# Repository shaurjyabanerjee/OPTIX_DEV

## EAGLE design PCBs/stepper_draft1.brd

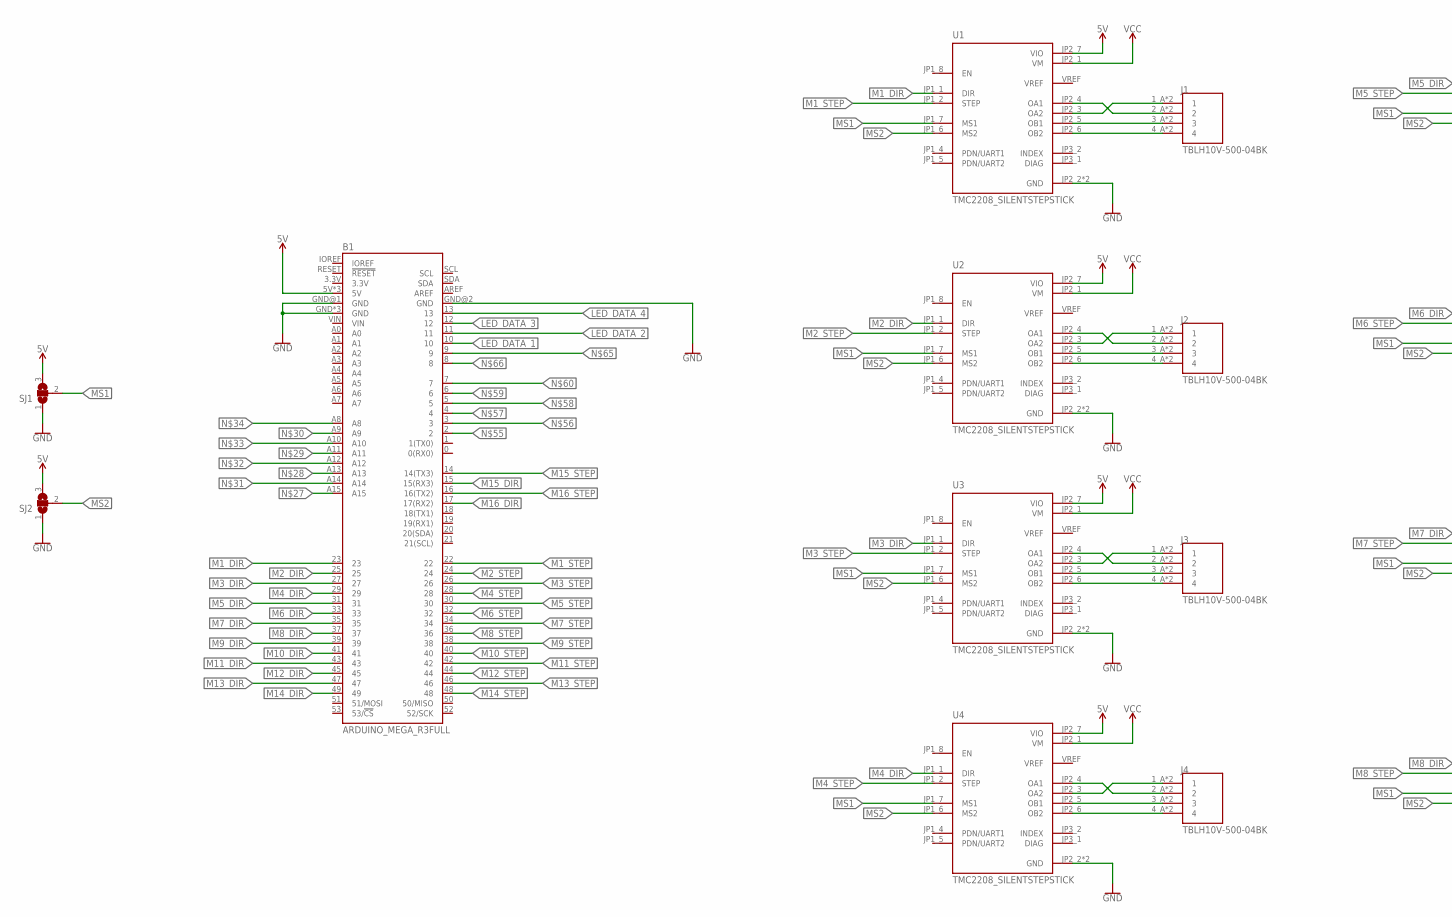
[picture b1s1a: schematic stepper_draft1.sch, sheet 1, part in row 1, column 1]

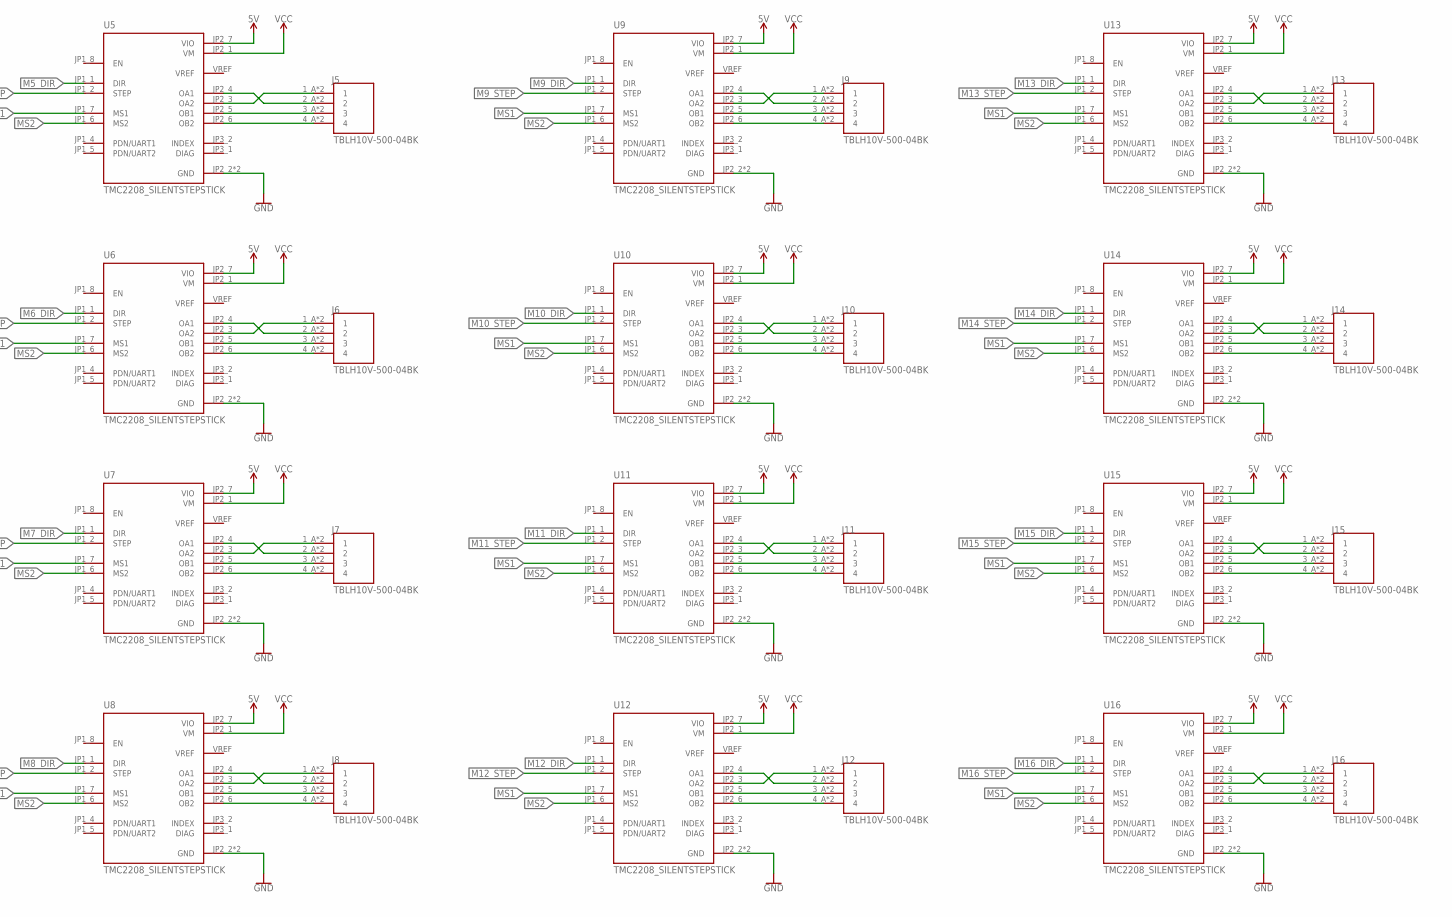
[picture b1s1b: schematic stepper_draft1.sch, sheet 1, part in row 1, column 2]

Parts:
B1: ARDUINO_MEGA_R3FULL; ARDUINO_MEGA_NO_SILK
J1, J2, J3, J4, J5, J6, J7, J8, J9, J10, J11, J12, J13, J14, J15, J16: TBLH10V-500-04BK; CUI_TBLH10V-500-04BK
SJ1, SJ2: SJ2W; SJ_2
U1, U2, U3, U4, U5, U6, U7, U8, U9, U10, U11, U12, U13, U14, U15, U16: TMC2208_SILENTSTEPSTICK; MODULE_TMC2208_SILENTSTEPSTICK

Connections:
5V: B1.5V, B1.5V@1 (5V), B1.5V@2 (5V), SJ1.3, SJ2.3, U1.JP2_7 (VIO), U2.JP2_7 (VIO), U3.JP2_7 (VIO), U4.JP2_7 (VIO), U5.JP2_7 (VIO), U6.JP2_7 (VIO), U7.JP2_7 (VIO), U8.JP2_7 (VIO), U9.JP2_7 (VIO), U10.JP2_7 (VIO), U11.JP2_7 (VIO), U12.JP2_7 (VIO), U13.JP2_7 (VIO), U14.JP2_7 (VIO), U15.JP2_7 (VIO), U16.JP2_7 (VIO)
GND: B1.GND, B1.GND@1 (GND), B1.GND@2 (GND), B1.GND@3 (GND), B1.GND@4 (GND), SJ1.1, SJ2.1, U1.JP2_2 (GND), U1.JP2_8 (GND), U2.JP2_2 (GND), U2.JP2_8 (GND), U3.JP2_2 (GND), U3.JP2_8 (GND), U4.JP2_2 (GND), U4.JP2_8 (GND), U5.JP2_2 (GND), U5.JP2_8 (GND), U6.JP2_2 (GND), U6.JP2_8 (GND), U7.JP2_2 (GND), U7.JP2_8 (GND), U8.JP2_2 (GND), U8.JP2_8 (GND), U9.JP2_2 (GND), U9.JP2_8 (GND), U10.JP2_2 (GND), U10.JP2_8 (GND), U11.JP2_2 (GND), U11.JP2_8 (GND), U12.JP2_2 (GND), U12.JP2_8 (GND), U13.JP2_2 (GND), U13.JP2_8 (GND), U14.JP2_2 (GND), U14.JP2_8 (GND), U15.JP2_2 (GND), U15.JP2_8 (GND), U16.JP2_2 (GND), U16.JP2_8 (GND); also elsewhere on the board
LED_DATA_1: B1.10; also elsewhere on the board
LED_DATA_2: B1.11; also elsewhere on the board
LED_DATA_3: B1.12; also elsewhere on the board
LED_DATA_4: B1.13; also elsewhere on the board
M1_DIR: B1.23, U1.JP1_1 (DIR)
M1_STEP: B1.22, U1.JP1_2 (STEP)
M2_DIR: B1.25, U2.JP1_1 (DIR)
M2_STEP: B1.24, U2.JP1_2 (STEP)
M3_DIR: B1.27, U3.JP1_1 (DIR)
M3_STEP: B1.26, U3.JP1_2 (STEP)
M4_DIR: B1.29, U4.JP1_1 (DIR)
M4_STEP: B1.28, U4.JP1_2 (STEP)
M5_DIR: B1.31, U5.JP1_1 (DIR)
M5_STEP: B1.30, U5.JP1_2 (STEP)
M6_DIR: B1.33, U6.JP1_1 (DIR)
M6_STEP: B1.32, U6.JP1_2 (STEP)
M7_DIR: B1.35, U7.JP1_1 (DIR)
M7_STEP: B1.34, U7.JP1_2 (STEP)
M8_DIR: B1.37, U8.JP1_1 (DIR)
M8_STEP: B1.36, U8.JP1_2 (STEP)
M9_DIR: B1.39, U9.JP1_1 (DIR)
M9_STEP: B1.38, U9.JP1_2 (STEP)
M10_DIR: B1.41, U10.JP1_1 (DIR)
M10_STEP: B1.40, U10.JP1_2 (STEP)
M11_DIR: B1.43, U11.JP1_1 (DIR)
M11_STEP: B1.42, U11.JP1_2 (STEP)
M12_DIR: B1.45, U12.JP1_1 (DIR)
M12_STEP: B1.44, U12.JP1_2 (STEP)
M13_DIR: B1.47, U13.JP1_1 (DIR)
M13_STEP: B1.46, U13.JP1_2 (STEP)
M14_DIR: B1.49, U14.JP1_1 (DIR)
M14_STEP: B1.48, U14.JP1_2 (STEP)
M15_DIR: B1.15 (15(RX3)), U15.JP1_1 (DIR)
M15_STEP: B1.14 (14(TX3)), U15.JP1_2 (STEP)
M16_DIR: B1.17 (17(RX2)), U16.JP1_1 (DIR)
M16_STEP: B1.16 (16(TX2)), U16.JP1_2 (STEP)
MS1: SJ1.2, U1.JP1_7 (MS1), U2.JP1_7 (MS1), U3.JP1_7 (MS1), U4.JP1_7 (MS1), U5.JP1_7 (MS1), U6.JP1_7 (MS1), U7.JP1_7 (MS1), U8.JP1_7 (MS1), U9.JP1_7 (MS1), U10.JP1_7 (MS1), U11.JP1_7 (MS1), U12.JP1_7 (MS1), U13.JP1_7 (MS1), U14.JP1_7 (MS1), U15.JP1_7 (MS1), U16.JP1_7 (MS1)
MS2: SJ2.2, U1.JP1_6 (MS2), U2.JP1_6 (MS2), U3.JP1_6 (MS2), U4.JP1_6 (MS2), U5.JP1_6 (MS2), U6.JP1_6 (MS2), U7.JP1_6 (MS2), U8.JP1_6 (MS2), U9.JP1_6 (MS2), U10.JP1_6 (MS2), U11.JP1_6 (MS2), U12.JP1_6 (MS2), U13.JP1_6 (MS2), U14.JP1_6 (MS2), U15.JP1_6 (MS2), U16.JP1_6 (MS2)
unnamed: J1.4_A (4), J1.4_B (4), U1.JP2_6 (OB2)
unnamed: J1.3_A (3), J1.3_B (3), U1.JP2_5 (OB1)
unnamed: J1.2_A (2), J1.2_B (2), U1.JP2_4 (OA1)
unnamed: J1.1_A (1), J1.1_B (1), U1.JP2_3 (OA2)
unnamed: J2.4_A (4), J2.4_B (4), U2.JP2_6 (OB2)
unnamed: J2.3_A (3), J2.3_B (3), U2.JP2_5 (OB1)
unnamed: J2.2_A (2), J2.2_B (2), U2.JP2_4 (OA1)
unnamed: J2.1_A (1), J2.1_B (1), U2.JP2_3 (OA2)
unnamed: J3.4_A (4), J3.4_B (4), U3.JP2_6 (OB2)
unnamed: J3.3_A (3), J3.3_B (3), U3.JP2_5 (OB1)
unnamed: J3.2_A (2), J3.2_B (2), U3.JP2_4 (OA1)
unnamed: J3.1_A (1), J3.1_B (1), U3.JP2_3 (OA2)
unnamed: J4.4_A (4), J4.4_B (4), U4.JP2_6 (OB2)
unnamed: J4.3_A (3), J4.3_B (3), U4.JP2_5 (OB1)
unnamed: J4.2_A (2), J4.2_B (2), U4.JP2_4 (OA1)
unnamed: J4.1_A (1), J4.1_B (1), U4.JP2_3 (OA2)
unnamed: J5.4_A (4), J5.4_B (4), U5.JP2_6 (OB2)
unnamed: J5.3_A (3), J5.3_B (3), U5.JP2_5 (OB1)
unnamed: J5.2_A (2), J5.2_B (2), U5.JP2_4 (OA1)
unnamed: J5.1_A (1), J5.1_B (1), U5.JP2_3 (OA2)
unnamed: J6.4_A (4), J6.4_B (4), U6.JP2_6 (OB2)
unnamed: J6.3_A (3), J6.3_B (3), U6.JP2_5 (OB1)
unnamed: J6.2_A (2), J6.2_B (2), U6.JP2_4 (OA1)
unnamed: J6.1_A (1), J6.1_B (1), U6.JP2_3 (OA2)
unnamed: J7.4_A (4), J7.4_B (4), U7.JP2_6 (OB2)
unnamed: J7.3_A (3), J7.3_B (3), U7.JP2_5 (OB1)
unnamed: J7.2_A (2), J7.2_B (2), U7.JP2_4 (OA1)
unnamed: J7.1_A (1), J7.1_B (1), U7.JP2_3 (OA2)
unnamed: J8.4_A (4), J8.4_B (4), U8.JP2_6 (OB2)
unnamed: J8.3_A (3), J8.3_B (3), U8.JP2_5 (OB1)
unnamed: J8.2_A (2), J8.2_B (2), U8.JP2_4 (OA1)
unnamed: J8.1_A (1), J8.1_B (1), U8.JP2_3 (OA2)
unnamed: J13.4_A (4), J13.4_B (4), U13.JP2_6 (OB2)
unnamed: J13.3_A (3), J13.3_B (3), U13.JP2_5 (OB1)
unnamed: J13.2_A (2), J13.2_B (2), U13.JP2_4 (OA1)
unnamed: J13.1_A (1), J13.1_B (1), U13.JP2_3 (OA2)
unnamed: J14.4_A (4), J14.4_B (4), U14.JP2_6 (OB2)
unnamed: J14.3_A (3), J14.3_B (3), U14.JP2_5 (OB1)
unnamed: J14.2_A (2), J14.2_B (2), U14.JP2_4 (OA1)
unnamed: J14.1_A (1), J14.1_B (1), U14.JP2_3 (OA2)
unnamed: J9.4_A (4), J9.4_B (4), U9.JP2_6 (OB2)
unnamed: J9.3_A (3), J9.3_B (3), U9.JP2_5 (OB1)
unnamed: J9.2_A (2), J9.2_B (2), U9.JP2_4 (OA1)
unnamed: J9.1_A (1), J9.1_B (1), U9.JP2_3 (OA2)
unnamed: J10.4_A (4), J10.4_B (4), U10.JP2_6 (OB2)
unnamed: J10.3_A (3), J10.3_B (3), U10.JP2_5 (OB1)
unnamed: J10.2_A (2), J10.2_B (2), U10.JP2_4 (OA1)
unnamed: J10.1_A (1), J10.1_B (1), U10.JP2_3 (OA2)
unnamed: J11.4_A (4), J11.4_B (4), U11.JP2_6 (OB2)
unnamed: J11.3_A (3), J11.3_B (3), U11.JP2_5 (OB1)
unnamed: J11.2_A (2), J11.2_B (2), U11.JP2_4 (OA1)
unnamed: J11.1_A (1), J11.1_B (1), U11.JP2_3 (OA2)
unnamed: J12.4_A (4), J12.4_B (4), U12.JP2_6 (OB2)
unnamed: J12.3_A (3), J12.3_B (3), U12.JP2_5 (OB1)
unnamed: J12.2_A (2), J12.2_B (2), U12.JP2_4 (OA1)
unnamed: J12.1_A (1), J12.1_B (1), U12.JP2_3 (OA2)
unnamed: J15.4_A (4), J15.4_B (4), U15.JP2_6 (OB2)
unnamed: J15.3_A (3), J15.3_B (3), U15.JP2_5 (OB1)
unnamed: J15.2_A (2), J15.2_B (2), U15.JP2_4 (OA1)
unnamed: J15.1_A (1), J15.1_B (1), U15.JP2_3 (OA2)
unnamed: J16.4_A (4), J16.4_B (4), U16.JP2_6 (OB2)
unnamed: J16.3_A (3), J16.3_B (3), U16.JP2_5 (OB1)
unnamed: J16.2_A (2), J16.2_B (2), U16.JP2_4 (OA1)
unnamed: J16.1_A (1), J16.1_B (1), U16.JP2_3 (OA2)
VCC: U1.JP2_1 (VM), U2.JP2_1 (VM), U3.JP2_1 (VM), U4.JP2_1 (VM), U5.JP2_1 (VM), U6.JP2_1 (VM), U7.JP2_1 (VM), U8.JP2_1 (VM), U9.JP2_1 (VM), U10.JP2_1 (VM), U11.JP2_1 (VM), U12.JP2_1 (VM), U13.JP2_1 (VM), U14.JP2_1 (VM), U15.JP2_1 (VM), U16.JP2_1 (VM)

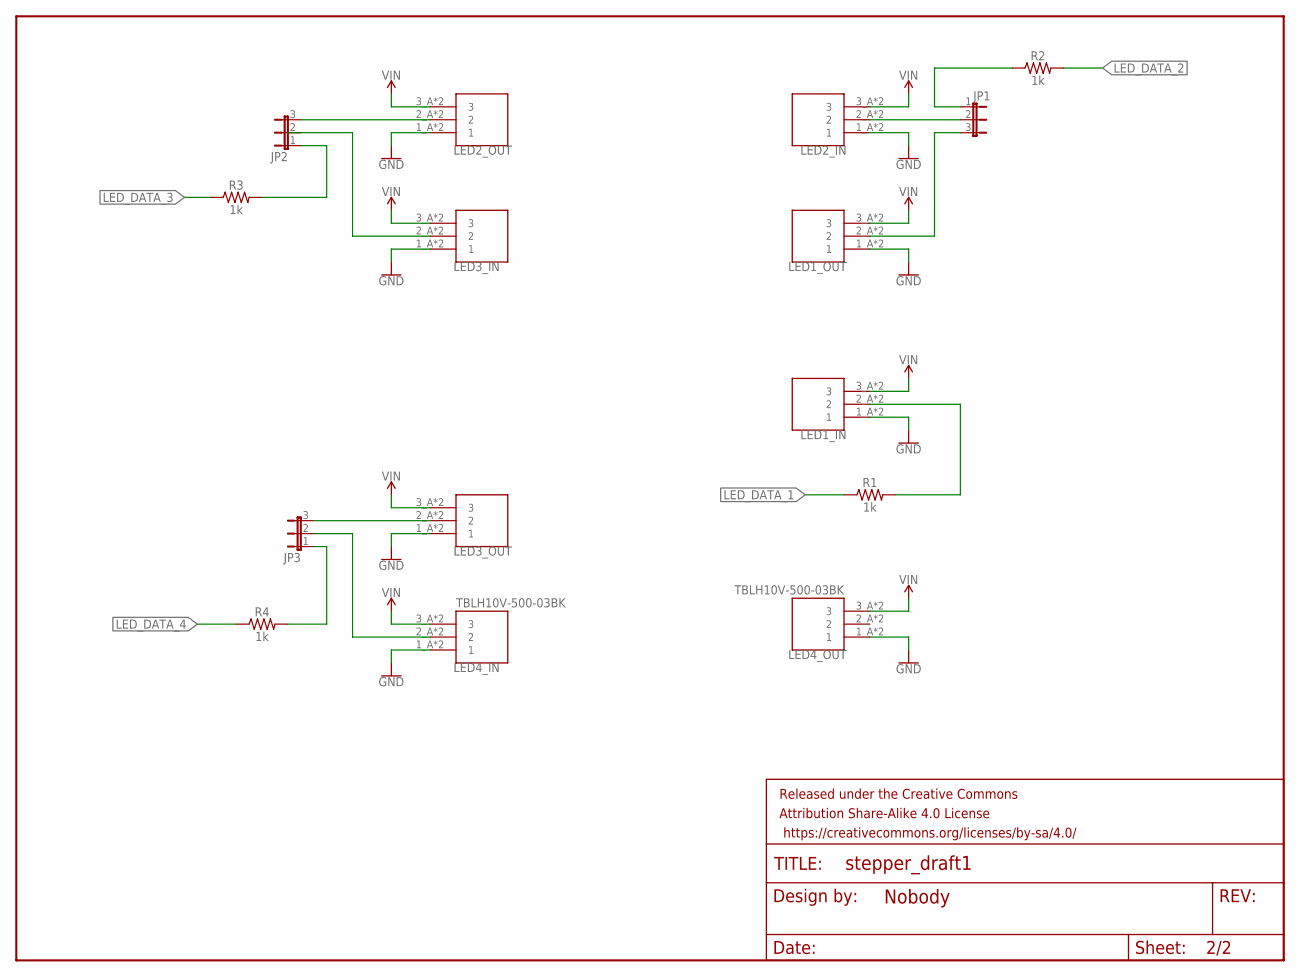
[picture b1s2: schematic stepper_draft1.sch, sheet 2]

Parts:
FRAME1: FRAME-LETTERNO_PACKAGE; DUMMY
JP1, JP2, JP3: JP2E; JP2
LED1_IN, LED1_OUT, LED2_IN, LED2_OUT, LED3_IN, LED3_OUT, LED4_IN, LED4_OUT: TBLH10V-500-03BK; CUI_TBLH10V-500-03BK
R1, R2, R3, R4: 1k; AXIAL-0.3

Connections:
GND: LED1_IN.1_A (1), LED1_IN.1_B (1), LED1_OUT.1_A (1), LED1_OUT.1_B (1), LED2_IN.1_A (1), LED2_IN.1_B (1), LED2_OUT.1_A (1), LED2_OUT.1_B (1), LED3_IN.1_A (1), LED3_IN.1_B (1), LED3_OUT.1_A (1), LED3_OUT.1_B (1), LED4_IN.1_A (1), LED4_IN.1_B (1), LED4_OUT.1_A (1), LED4_OUT.1_B (1); also elsewhere on the board
LED_DATA_1: R1.P$1 (1); also elsewhere on the board
LED_DATA_2: R2.P$2 (2); also elsewhere on the board
LED_DATA_3: R3.P$1 (1); also elsewhere on the board
LED_DATA_4: R4.P$1 (1); also elsewhere on the board
unnamed: LED1_IN.2_A (2), LED1_IN.2_B (2), R1.P$2 (2)
unnamed: JP1.3, LED1_OUT.2_A (2), LED1_OUT.2_B (2)
unnamed: JP1.1, R2.P$1 (1)
unnamed: JP1.2, LED2_IN.2_A (2), LED2_IN.2_B (2)
unnamed: JP2.3, LED2_OUT.2_A (2), LED2_OUT.2_B (2)
unnamed: JP2.1, R3.P$2 (2)
unnamed: JP2.2, LED3_IN.2_A (2), LED3_IN.2_B (2)
unnamed: JP3.1, R4.P$2 (2)
unnamed: JP3.3, LED3_OUT.2_A (2), LED3_OUT.2_B (2)
unnamed: JP3.2, LED4_IN.2_A (2), LED4_IN.2_B (2)
VIN: LED1_IN.3_A (3), LED1_IN.3_B (3), LED1_OUT.3_A (3), LED1_OUT.3_B (3), LED2_IN.3_A (3), LED2_IN.3_B (3), LED2_OUT.3_A (3), LED2_OUT.3_B (3), LED3_IN.3_A (3), LED3_IN.3_B (3), LED3_OUT.3_A (3), LED3_OUT.3_B (3), LED4_IN.3_A (3), LED4_IN.3_B (3), LED4_OUT.3_A (3), LED4_OUT.3_B (3)

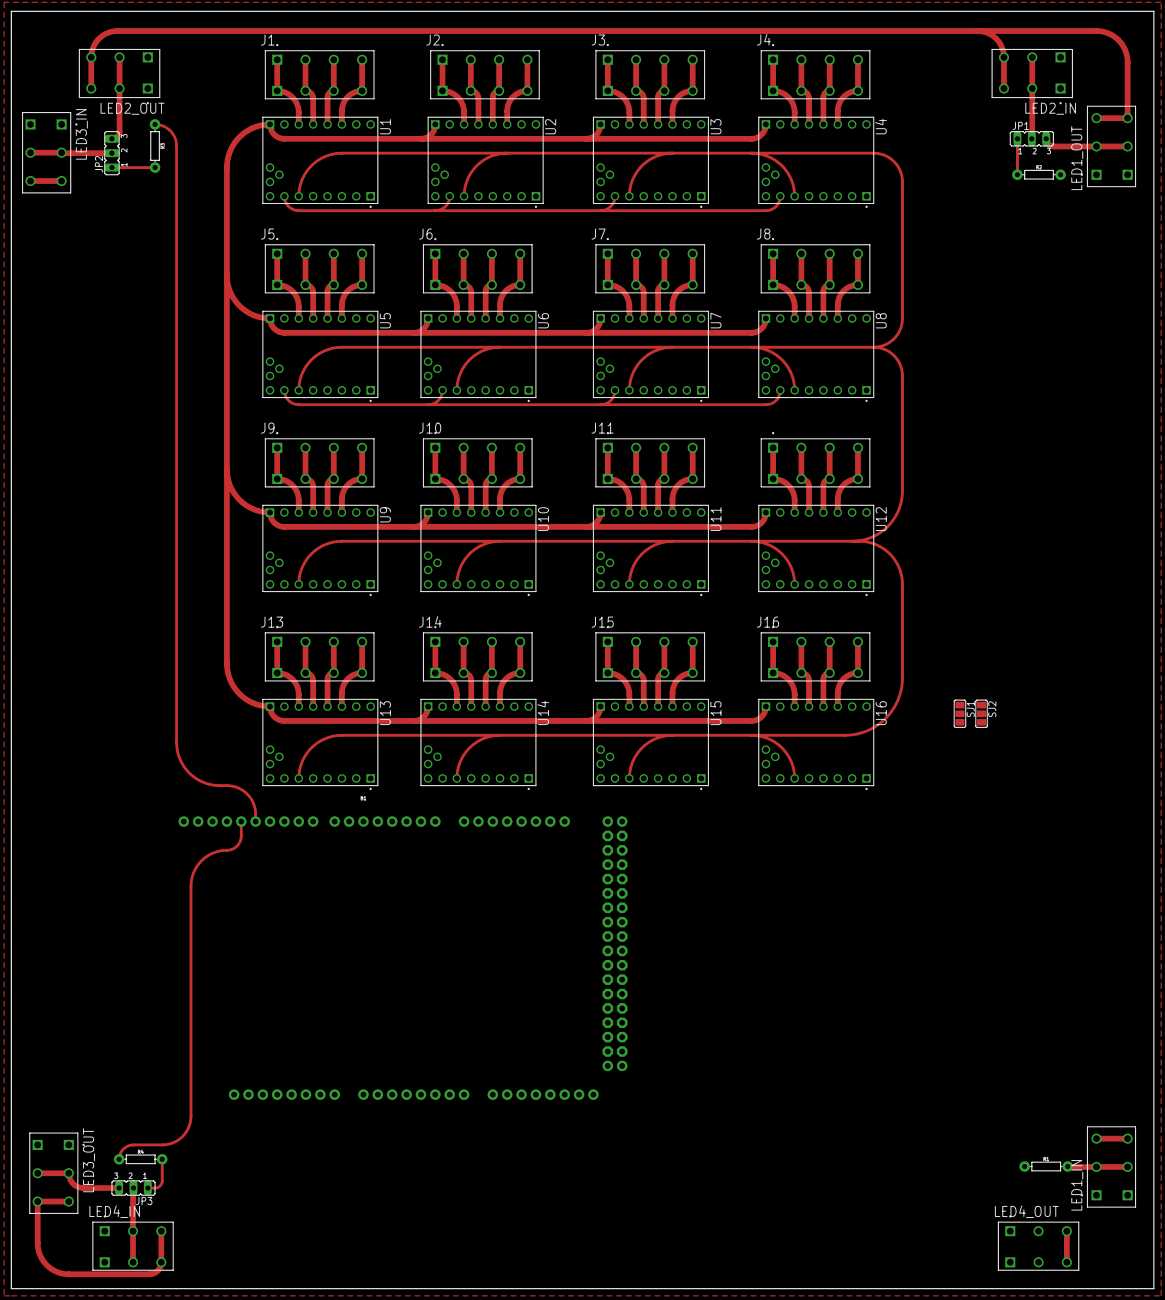
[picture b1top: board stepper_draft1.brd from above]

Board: 2 copper layers, 201.9 x 225.7 mm, 51 parts (0 on the bottom side), 116 nets.

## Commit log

2022-05-15 Update OPTIX_CONTROL_V0.pde
    added LED color picker, and associated packet support
2022-05-16 Fixed directory structure. Added STLs and laser artwork
2022-05-17 Update OPTIX_CONTROL_V0.pde
    Added feature to home all 16 motors at once.
2022-05-17 Added jog by 15 and 5 degree steps per motor to make homing easier
2022-05-17 Added first EAGLE draft for stepper control shield V0
2022-06-16 added per pixel led control over serial
    added per pixel led control over serial
2022-06-16 added modular neopixel data routing to schematic
    added modular neopixel data routing to schematic
2022-06-16 minor PCB updates
    minor PCB updates
2022-06-16 added and tested sending scaled random colors to each pixel
    added and tested sending scaled random colors to each pixel
2022-06-16 implemented sending gradients to neopixels over serial
    implemented sending gradients to neopixels over serial
2022-06-17 finally added to random 45s command functionality
    finally added to random 45s command functionality
2022-06-17 added all 16 stepper drive packages to pcb
    added all 16 stepper drive packages to pcb
2022-06-17 started top layer routing
    started top layer routing

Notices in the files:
parts and their libraries:
SparkFun-Boards: Licensing: Creative Commons ShareAlike 4.0 International - https://creativecommons.org/licenses/by-sa/4.0
SparkFun-Aesthetics: Released under the Creative Commons Attribution Share-Alike 4.0 License
SparkFun-Aesthetics: https://creativecommons.org/licenses/by-sa/4.0
